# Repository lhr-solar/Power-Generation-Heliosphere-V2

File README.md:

# Power-Generation-Heliosphere-V2
Tong's Project

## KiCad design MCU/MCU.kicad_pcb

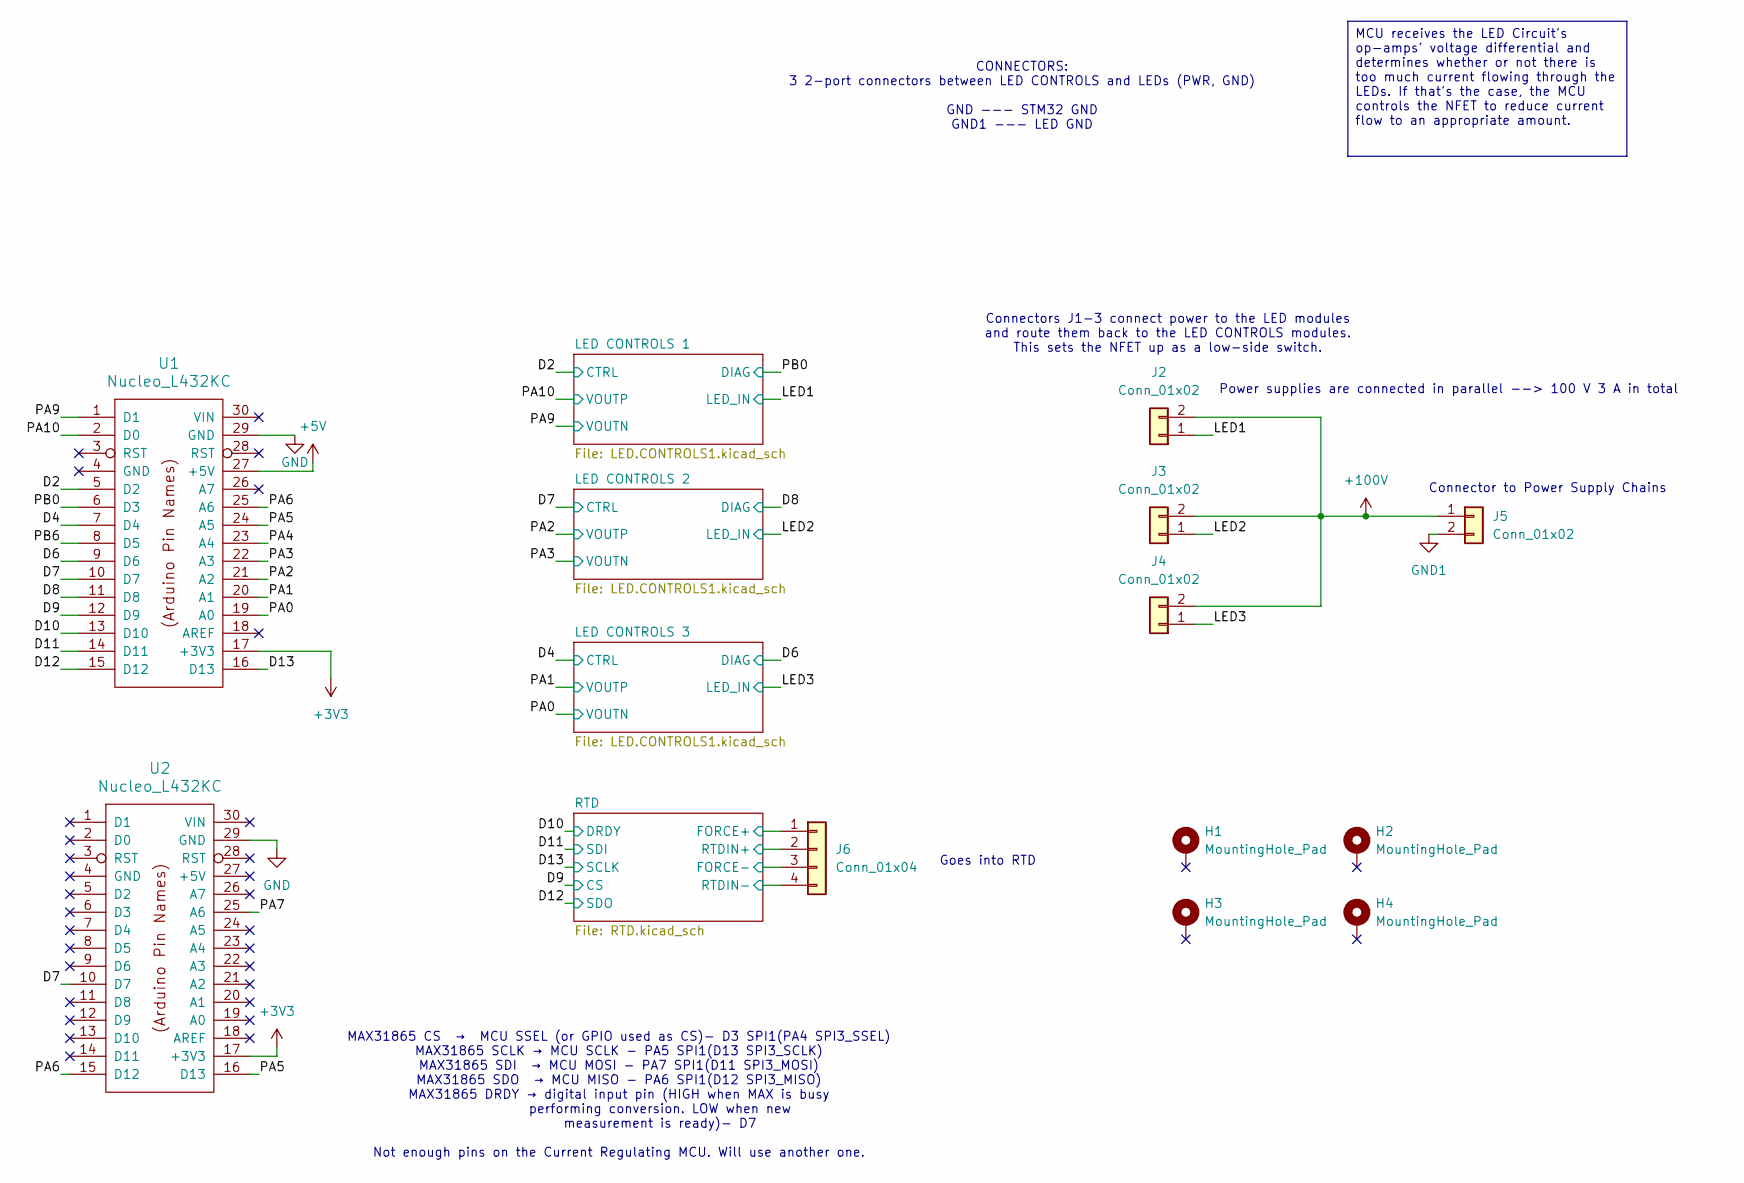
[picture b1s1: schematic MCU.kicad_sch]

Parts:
H1, H2, H3, H4: MountingHole_Pad; MountingHole_3.2mm_M3_Pad_TopBottom
J2, J3, J4, J5: Conn_01x02; JST_VH_B2P-VH_1x02_P3.96mm_Vertical
J6: Conn_01x04; JST_EH_B4B-EH-A_1x04_P2.50mm_Vertical
U1, U2: Nucleo_L432KC; NucleoL432KC

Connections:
+3V3: U1.17 (+3V3), U2.17 (+3V3); also elsewhere on the board
+5V: U1.27 (+5V)
+100V: J2.2, J3.2, J4.2, J5.1
/D2: U1.5 (D2); also elsewhere on the board
/D4: U1.7 (D4); also elsewhere on the board
/D6: U1.9 (D6); also elsewhere on the board
/D7: U1.10 (D7), U2.10 (D7); also elsewhere on the board
/D8: U1.11 (D8); also elsewhere on the board
/D9: U1.12 (D9); also elsewhere on the board
/D10: U1.13 (D10); also elsewhere on the board
/D11: U1.14 (D11); also elsewhere on the board
/D12: U1.15 (D12); also elsewhere on the board
/D13: U1.16 (D13); also elsewhere on the board
/LED1: J2.1; also elsewhere on the board
/LED2: J3.1; also elsewhere on the board
/LED3: J4.1; also elsewhere on the board
/PA0: U1.19 (A0); also elsewhere on the board
/PA1: U1.20 (A1); also elsewhere on the board
/PA2: U1.21 (A2); also elsewhere on the board
/PA3: U1.22 (A3); also elsewhere on the board
/PA4: U1.23 (A4)
/PA5: U1.24 (A5), U2.16 (D13)
/PA6: U1.25 (A6), U2.15 (D12)
/PA9: U1.1 (D1); also elsewhere on the board
/PA10: U1.2 (D0); also elsewhere on the board
/PB0: U1.6 (D3); also elsewhere on the board
/PB6: U1.8 (D5)
/RTD/FORCE+: J6.1; also elsewhere on the board
/RTD/FORCE-: J6.3; also elsewhere on the board
/RTD/RTDIN+: J6.2; also elsewhere on the board
/RTD/RTDIN-: J6.4; also elsewhere on the board
GND: U1.29 (GND), U2.29 (GND); also elsewhere on the board
GND1: J5.2; also elsewhere on the board

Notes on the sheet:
MAX31865 CS → MCU SSEL (or GPIO used as CS)- D3 SPI1(PA4 SPI3_SSEL) MAX31865 SCLK → MCU SCLK - PA5 SPI1(D13 SPI3_SCLK) MAX31865 SDI → MCU MOSI - PA7 SPI1(D11 SPI3_MOSI) MAX31865 SDO → MCU MISO - PA6 SPI1(D12 SPI3_MISO) MAX31865 DRDY → digital input pin (HIGH when MAX is busy performing conversion. 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
Goes into RTD
CONNECTORS: 3 2-port connectors between LED CONTROLS and LEDs (PWR, GND) GND --- STM32 GND GND1 --- LED GND
Power supplies are connected in parallel --> 100 V 3 A in total
Connector to Power Supply Chains
Connectors J1-3 connect power to the LED modules and route them back to the LED CONTROLS modules. This sets the NFET up as a low-side switch.
MCU receives the LED Circuit's op-amps' voltage differential and determines whether or not there is too much current flowing through the LEDs. If that's the case, the MCU controls the NFET to reduce current flow to an appropriate amount.

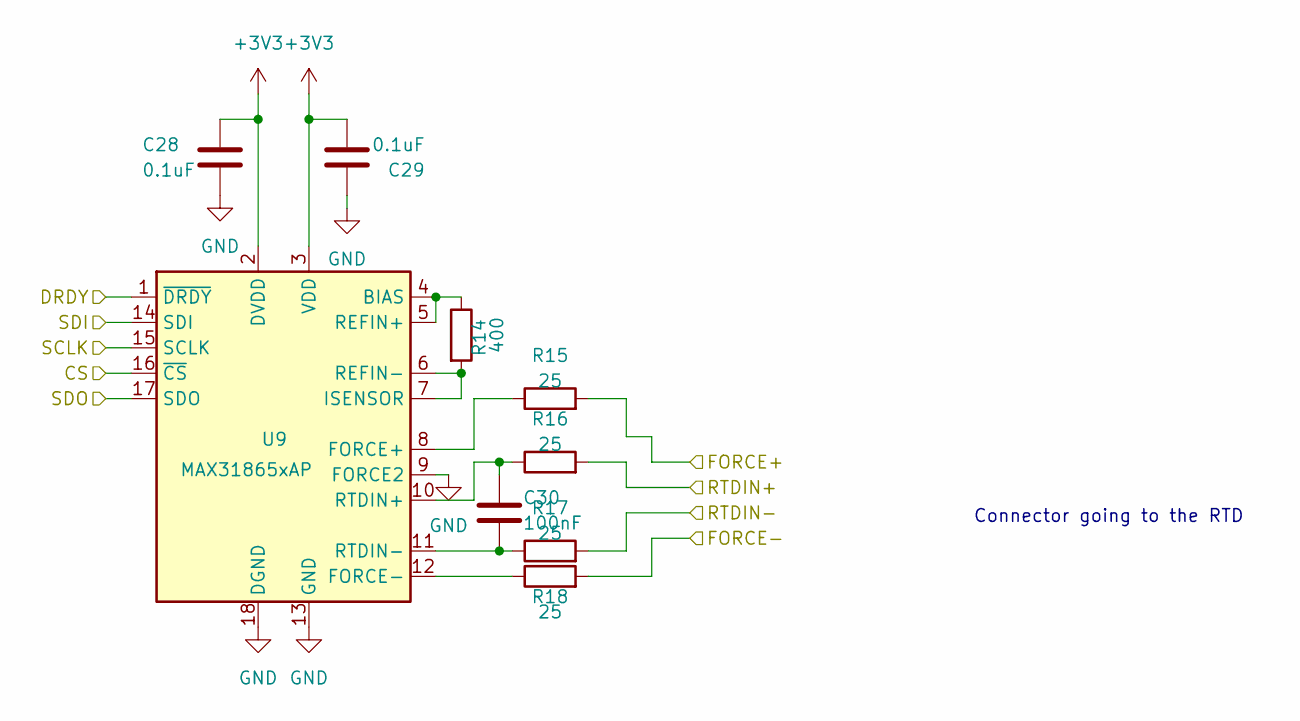
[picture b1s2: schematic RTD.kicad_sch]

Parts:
C28, C29: 0.1uF; C_0603_1608Metric_Pad1.08x0.95mm_HandSolder
C30: 100nF; C_1206_3216Metric_Pad1.33x1.80mm_HandSolder
R14: 400; R_0603_1608Metric_Pad0.98x0.95mm_HandSolder
R15, R16, R17, R18: 25; R_0603_1608Metric_Pad0.98x0.95mm_HandSolder
U9: MAX31865xAP; SSOP-20_5.3x7.2mm_P0.65mm

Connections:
+3V3: C28.2, C29.1, U9.2 (DVDD), U9.3 (VDD); also elsewhere on the board
/D9: U9.16 (~CS); also elsewhere on the board
/D10: U9.1 (~DRDY); also elsewhere on the board
/D11: U9.14 (SDI); also elsewhere on the board
/D12: U9.17 (SDO); also elsewhere on the board
/D13: U9.15 (SCLK); also elsewhere on the board
/RTD/FORCE+: R15.2; also elsewhere on the board
/RTD/FORCE-: R18.2; also elsewhere on the board
/RTD/RTDIN+: R16.2; also elsewhere on the board
/RTD/RTDIN-: R17.2; also elsewhere on the board
GND: C28.1, C29.2, U9.9 (FORCE2), U9.13 (GND), U9.18 (DGND), U9.19 (GND); also elsewhere on the board
unnamed: R14.1, U9.4 (BIAS), U9.5 (REFIN+)
unnamed: R15.1, U9.8 (FORCE+)
unnamed: R18.1, U9.12 (FORCE-)
unnamed: R14.2, U9.6 (REFIN-), U9.7 (ISENSOR)
unnamed: C30.2, R16.1, U9.10 (RTDIN+)
unnamed: C30.1, R17.1, U9.11 (RTDIN-)

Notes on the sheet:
Connector going to the RTD

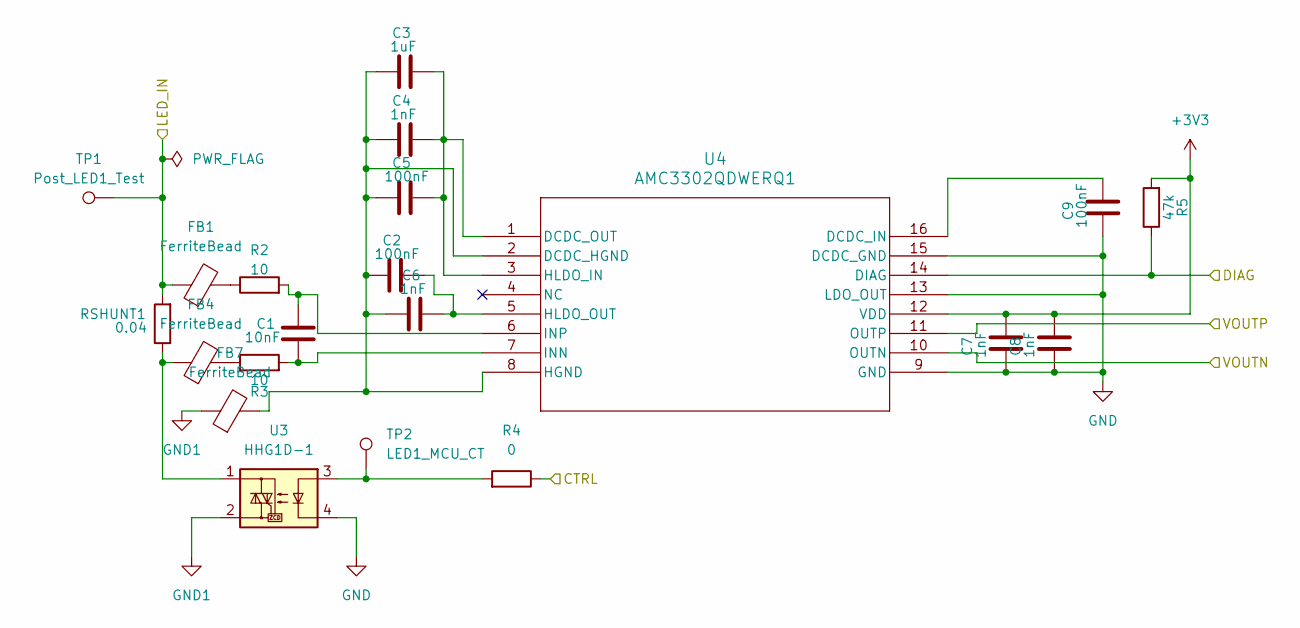
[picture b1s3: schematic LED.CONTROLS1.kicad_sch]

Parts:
C1: 10nF; C_1206_3216Metric
C2, C5, C9: 100nF; C_0603_1608Metric_Pad1.08x0.95mm_HandSolder
C3: 1uF; C_0603_1608Metric_Pad1.08x0.95mm_HandSolder
C4, C6, C7, C8: 1nF; C_0603_1608Metric_Pad1.08x0.95mm_HandSolder
FB1, FB4, FB7: FerriteBead; R_0603_1608Metric_Pad0.98x0.95mm_HandSolder
R2, R3: 10; R_0603_1608Metric_Pad0.98x0.95mm_HandSolder
R4: 0; R_0603_1608Metric_Pad0.98x0.95mm_HandSolder
R5: 47k; R_0603_1608Metric_Pad0.98x0.95mm_HandSolder
RSHUNT1: 0.04; R_2512_6332Metric_Pad1.40x3.35mm_HandSolder
TP1: Post_LED1_Test; TestPoint_Pad_2.0x2.0mm
TP2: LED1_MCU_CT; TestPoint_Pad_1.5x1.5mm
U3: HHG1D-1; Relay_NCR_HHG1D-1
U4: AMC3302QDWERQ1; SOIC-3302DWERQ1_TEX

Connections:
+3V3: C7.1, C8.1, R5.2, U4.12 (VDD); also elsewhere on the board
/D2: R4.1; also elsewhere on the board
/LED1: FB1.1, RSHUNT1.2, TP1.1; also elsewhere on the board
/PA9: U4.10 (OUTN); also elsewhere on the board
/PA10: U4.11 (OUTP); also elsewhere on the board
/PB0: R5.1, U4.14 (DIAG); also elsewhere on the board
GND: C7.2, C8.2, C9.2, U3.4, U4.9 (GND), U4.13 (LDO_OUT), U4.15 (DCDC_GND); also elsewhere on the board
GND1: FB7.1, U3.2; also elsewhere on the board
unnamed: FB1.2, R2.1
unnamed: FB4.1, RSHUNT1.1, U3.1
unnamed: FB4.2, R3.1
unnamed: R4.2, TP2.1, U3.3
unnamed: C2.2, C3.2, C4.2, C5.2, C6.2, FB7.2, U4.2 (DCDC_HGND), U4.8 (HGND)
unnamed: C9.1, U4.16 (DCDC_IN)
unnamed: C3.1, C4.1, C5.1, U4.1 (DCDC_OUT), U4.3 (HLDO_IN)
unnamed: C2.1, C6.1, U4.5 (HLDO_OUT)
unnamed: C1.2, R3.2, U4.7 (INN)
unnamed: C1.1, R2.2, U4.6 (INP)

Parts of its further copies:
C10, C19: 10nF; C_1206_3216Metric
C11, C14, C18, C20, C23, C27: 100nF; C_0603_1608Metric_Pad1.08x0.95mm_HandSolder
C12, C21: 1uF; C_0603_1608Metric_Pad1.08x0.95mm_HandSolder
C13, C15, C16, C17, C22, C24, C25, C26: 1nF; C_0603_1608Metric_Pad1.08x0.95mm_HandSolder
FB2, FB3, FB5, FB6, FB8, FB9: FerriteBead; R_0603_1608Metric_Pad0.98x0.95mm_HandSolder
R6, R7, R10, R11: 10; R_0603_1608Metric_Pad0.98x0.95mm_HandSolder
R8, R12: 0; R_0603_1608Metric_Pad0.98x0.95mm_HandSolder
R9, R13: 47k; R_0603_1608Metric_Pad0.98x0.95mm_HandSolder
RSHUNT2, RSHUNT3: 0.04; R_2512_6332Metric_Pad1.40x3.35mm_HandSolder
TP3, TP5: Post_LED1_Test; TestPoint_Pad_2.0x2.0mm
TP4, TP6: LED1_MCU_CT; TestPoint_Pad_1.5x1.5mm
U5, U7: HHG1D-1; Relay_NCR_HHG1D-1
U6, U8: AMC3302QDWERQ1; SOIC-3302DWERQ1_TEX

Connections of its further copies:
+3V3: C16.1, C17.1, C25.1, C26.1, R9.2, R13.2, U6.12 (VDD), U8.12 (VDD); also elsewhere on the board
/D4: R12.1; also elsewhere on the board
/D6: R13.1, U8.14 (DIAG); also elsewhere on the board
/D7: R8.1; also elsewhere on the board
/D8: R9.1, U6.14 (DIAG); also elsewhere on the board
/LED2: FB2.1, RSHUNT2.2, TP3.1; also elsewhere on the board
/LED3: FB3.1, RSHUNT3.2, TP5.1; also elsewhere on the board
/PA0: U8.10 (OUTN); also elsewhere on the board
/PA1: U8.11 (OUTP); also elsewhere on the board
/PA2: U6.11 (OUTP); also elsewhere on the board
/PA3: U6.10 (OUTN); also elsewhere on the board
GND: C16.2, C17.2, C18.2, C25.2, C26.2, C27.2, U5.4, U6.9 (GND), U6.13 (LDO_OUT), U6.15 (DCDC_GND), U7.4, U8.9 (GND), U8.13 (LDO_OUT), U8.15 (DCDC_GND); also elsewhere on the board
GND1: FB8.1, FB9.1, U5.2, U7.2; also elsewhere on the board
unnamed: FB2.2, R6.1
unnamed: FB3.2, R10.1
unnamed: FB5.1, RSHUNT2.1, U5.1
unnamed: FB5.2, R7.1
unnamed: FB6.1, RSHUNT3.1, U7.1
unnamed: FB6.2, R11.1
unnamed: R8.2, TP4.1, U5.3
unnamed: R12.2, TP6.1, U7.3
unnamed: C11.2, C12.2, C13.2, C14.2, C15.2, FB8.2, U6.2 (DCDC_HGND), U6.8 (HGND)
unnamed: C18.1, U6.16 (DCDC_IN)
unnamed: C12.1, C13.1, C14.1, U6.1 (DCDC_OUT), U6.3 (HLDO_IN)
unnamed: C11.1, C15.1, U6.5 (HLDO_OUT)
unnamed: C10.2, R7.2, U6.7 (INN)
unnamed: C10.1, R6.2, U6.6 (INP)
unnamed: C20.2, C21.2, C22.2, C23.2, C24.2, FB9.2, U8.2 (DCDC_HGND), U8.8 (HGND)
unnamed: C27.1, U8.16 (DCDC_IN)
unnamed: C21.1, C22.1, C23.1, U8.1 (DCDC_OUT), U8.3 (HLDO_IN)
unnamed: C20.1, C24.1, U8.5 (HLDO_OUT)
unnamed: C19.2, R11.2, U8.7 (INN)
unnamed: C19.1, R10.2, U8.6 (INP)

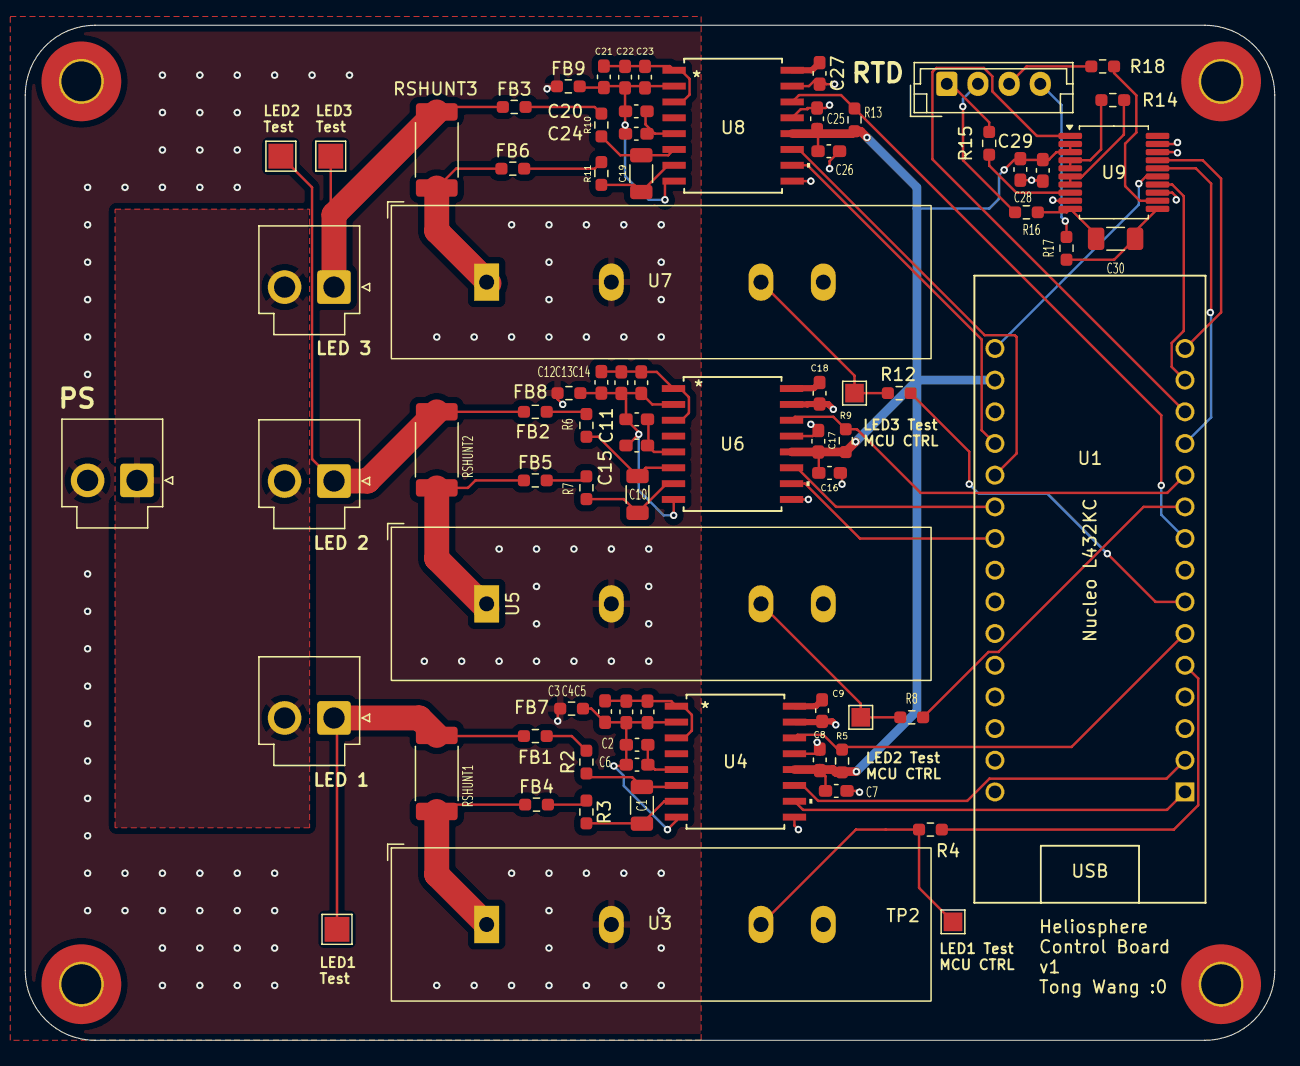
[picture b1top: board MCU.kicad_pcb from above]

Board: 2 copper layers, 100.2 x 81.4 mm, 82 parts (0 on the bottom side), 64 nets.

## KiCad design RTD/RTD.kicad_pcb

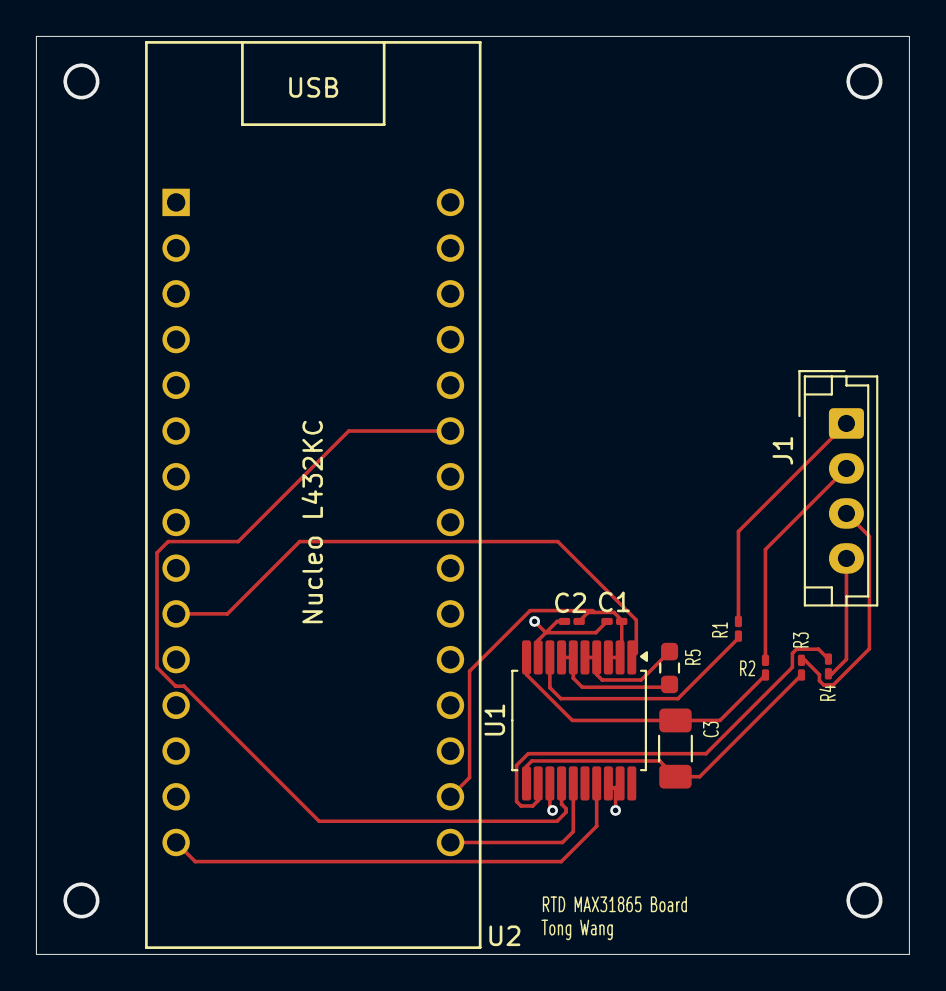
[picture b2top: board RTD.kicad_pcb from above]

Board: 2 copper layers, 48.5 x 51.0 mm, 11 parts (0 on the bottom side), 16 nets.

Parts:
C1, C2: 0.1uF; C_0201_0603Metric_Pad0.64x0.40mm_HandSolder
C3: 100nF; C_1206_3216Metric_Pad1.33x1.80mm_HandSolder
J1: Conn_01x04; JST_EH_B4B-EH-A_1x04_P2.50mm_Vertical
R1, R2, R3, R4: 25; R_0201_0603Metric_Pad0.64x0.40mm_HandSolder
R5: 400; R_0603_1608Metric_Pad0.98x0.95mm_HandSolder
U1: MAX31865xAP; SSOP-20_5.3x7.2mm_P0.65mm
U2: Nucleo_L432KC; NucleoL432KC

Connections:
+3V3: C1.2, C2.1, U1.2 (DVDD), U1.3 (VDD), U2.17 (+3V3)
/D7: U1.1 (~DRDY), U2.10 (D7)
/PA5: U1.15 (SCLK), U2.16 (D13)
/PA6: U1.17 (SDO), U2.15 (D12)
/PA7: U1.14 (SDI), U2.25 (A6)
GND: C1.1, C2.2, U1.9 (FORCE2), U1.13 (GND), U1.18 (DGND), U1.19 (GND), U2.29 (GND)
unnamed: J1.1, R1.2
unnamed: J1.2, R2.2
unnamed: J1.3, R3.2
unnamed: J1.4, R4.2
unnamed: R5.1, U1.4 (BIAS), U1.5 (REFIN+)
unnamed: R1.1, U1.8 (FORCE+)
unnamed: R4.1, U1.12 (FORCE-)
unnamed: R5.2, U1.6 (REFIN-), U1.7 (ISENSOR)
unnamed: C3.2, R2.1, U1.10 (RTDIN+)
unnamed: C3.1, R3.1, U1.11 (RTDIN-)

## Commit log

2024-11-16 Constant Current Driver Revision 1
2024-11-16 utsvt kicad library
2024-11-16 hello
2024-12-07 finished schematic!
2025-02-26 Heliosphere v1.2
2025-04-09 Heliosphere 1.3
2025-09-18 heliospherev1.4
2025-09-27 Centralized isolation amp power source. Corrected STM32 pins.
2025-10-04 Assigned footprints and added RTD
2025-10-11 Finalized schematic and started layout
2025-10-13 MCU Layout V1
2025-10-21 Adjusted trace widths. Added ferrite beads. Changed connectors to fit new trace widths. Added +3V3 fill zone in B.Cu. Fixed silkscreen placements.
2025-10-24 Finished RTD schematic and layout. Got rid of RTD part of MCU.
2025-10-25 layout suggestions
2025-10-29 Cleaned up traces in MCU layout
2025-11-08 layout changes
2025-11-09 almost done with MCU: need to change TP names, adjust RTD on MCU
2025-11-09 fixed previous changes; should be good to order
2025-11-12 final?
2025-11-15 layout fixes
2025-11-15 increased footprint sizes
2025-11-15 fixed ferrite bead size
2025-11-15 final changes
2025-11-15 silkscreen, edge cuts, other stuff fixes
